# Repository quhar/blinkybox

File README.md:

# Bruno's BlinkyBox
Arduino based light toy. Inspired and based on https://github.com/miria/BlinkyBox.

## Overview

This is a battery powered device which displays various light effects. They are controlled using rotary knobs and arcade style buttons.

One knob is used to change the effect, the other one allows to iterate over spectrum of colors (64 colors in total). Buttons are used to select different colors. Knob switches are wired, but not used at the moment.

## Parts list
* Arduino Nano
* Clear project box - https://smile.amazon.com/gp/product/B00HKIQUCC
* Arcade buttons - https://smile.amazon.com/gp/product/B08JHVLK84
* Rotary encoder knobs - https://smile.amazon.com/gp/product/B07F26CT6B/
* Individually addressable LEDs - https://smile.amazon.com/gp/product/B01CDTECSG
* SparkFun LiPo charger/booster - https://www.sparkfun.com/products/14411
* 3700 mAh LiPo battery - https://smile.amazon.com/gp/product/B08215B4KK
* Custom PCB fabbed in OSHPark - https://oshpark.com/shared_projects/V4KbTRDu
* Screw block terminals
* On/Off switch
* Hot glue

Of course all parts can be swapped to something that suits better.

## PCB

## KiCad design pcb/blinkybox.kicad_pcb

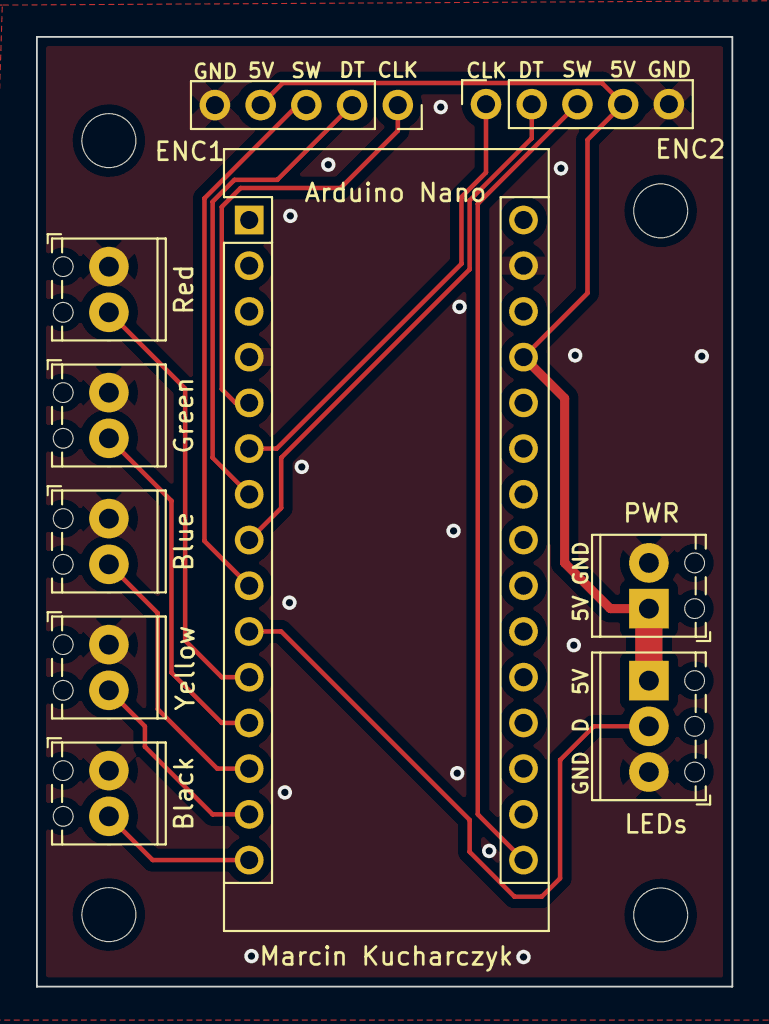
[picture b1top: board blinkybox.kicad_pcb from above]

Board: 2 copper layers, 38.6 x 52.8 mm, 10 parts (0 on the bottom side), 14 nets.

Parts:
Arduino Nano: Arduino_Nano_v3.x; Arduino_Nano
Black: Black; TerminalBlock_Phoenix_MPT-0,5-2-2.54_1x02_P2.54mm_Horizontal
Blue: Blue; TerminalBlock_Phoenix_MPT-0,5-2-2.54_1x02_P2.54mm_Horizontal
ENC1: Rotary Enc 1; PinSocket_1x05_P2.54mm_Vertical
ENC2: Rotary Enc 2; PinSocket_1x05_P2.54mm_Vertical
Green: Green; TerminalBlock_Phoenix_MPT-0,5-2-2.54_1x02_P2.54mm_Horizontal
LEDs: LED; TerminalBlock_Phoenix_MPT-0,5-3-2.54_1x03_P2.54mm_Horizontal
PWR: Screw_Terminal_01x02; TerminalBlock_Phoenix_MPT-0,5-2-2.54_1x02_P2.54mm_Horizontal
Red: Red; TerminalBlock_Phoenix_MPT-0,5-2-2.54_1x02_P2.54mm_Horizontal
Yellow: Yellow; TerminalBlock_Phoenix_MPT-0,5-2-2.54_1x02_P2.54mm_Horizontal

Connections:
+5V: Arduino Nano.27 (+5V), ENC1.4 (VCC), ENC2.4 (VCC), LEDs.3, PWR.1
GND: Arduino Nano.4 (GND), Arduino Nano.29 (GND), Black.1, Blue.1, ENC1.5 (GND), ENC2.5 (GND), Green.1, LEDs.1, PWR.2, Red.1, Yellow.1
unnamed: Arduino Nano.5 (D2), ENC1.1 (CLK)
unnamed: Arduino Nano.6 (D3), ENC2.1 (CLK)
unnamed: Arduino Nano.7 (D4), ENC1.2 (DT)
unnamed: Arduino Nano.8 (D5), ENC2.2 (DT)
unnamed: Arduino Nano.10 (D7), LEDs.2
unnamed: Arduino Nano.11 (D8), Red.2
unnamed: Arduino Nano.12 (D9), Green.2
unnamed: Arduino Nano.13 (D10), Blue.2
unnamed: Arduino Nano.14 (D11), Yellow.2
unnamed: Arduino Nano.15 (D12), Black.2
unnamed: Arduino Nano.9 (D6), ENC1.3 (SW)
unnamed: Arduino Nano.16 (D13), ENC2.3 (SW)

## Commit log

2022-06-14 Added Arduino code and KiCad files
2022-06-14 Added 3D rendering image
